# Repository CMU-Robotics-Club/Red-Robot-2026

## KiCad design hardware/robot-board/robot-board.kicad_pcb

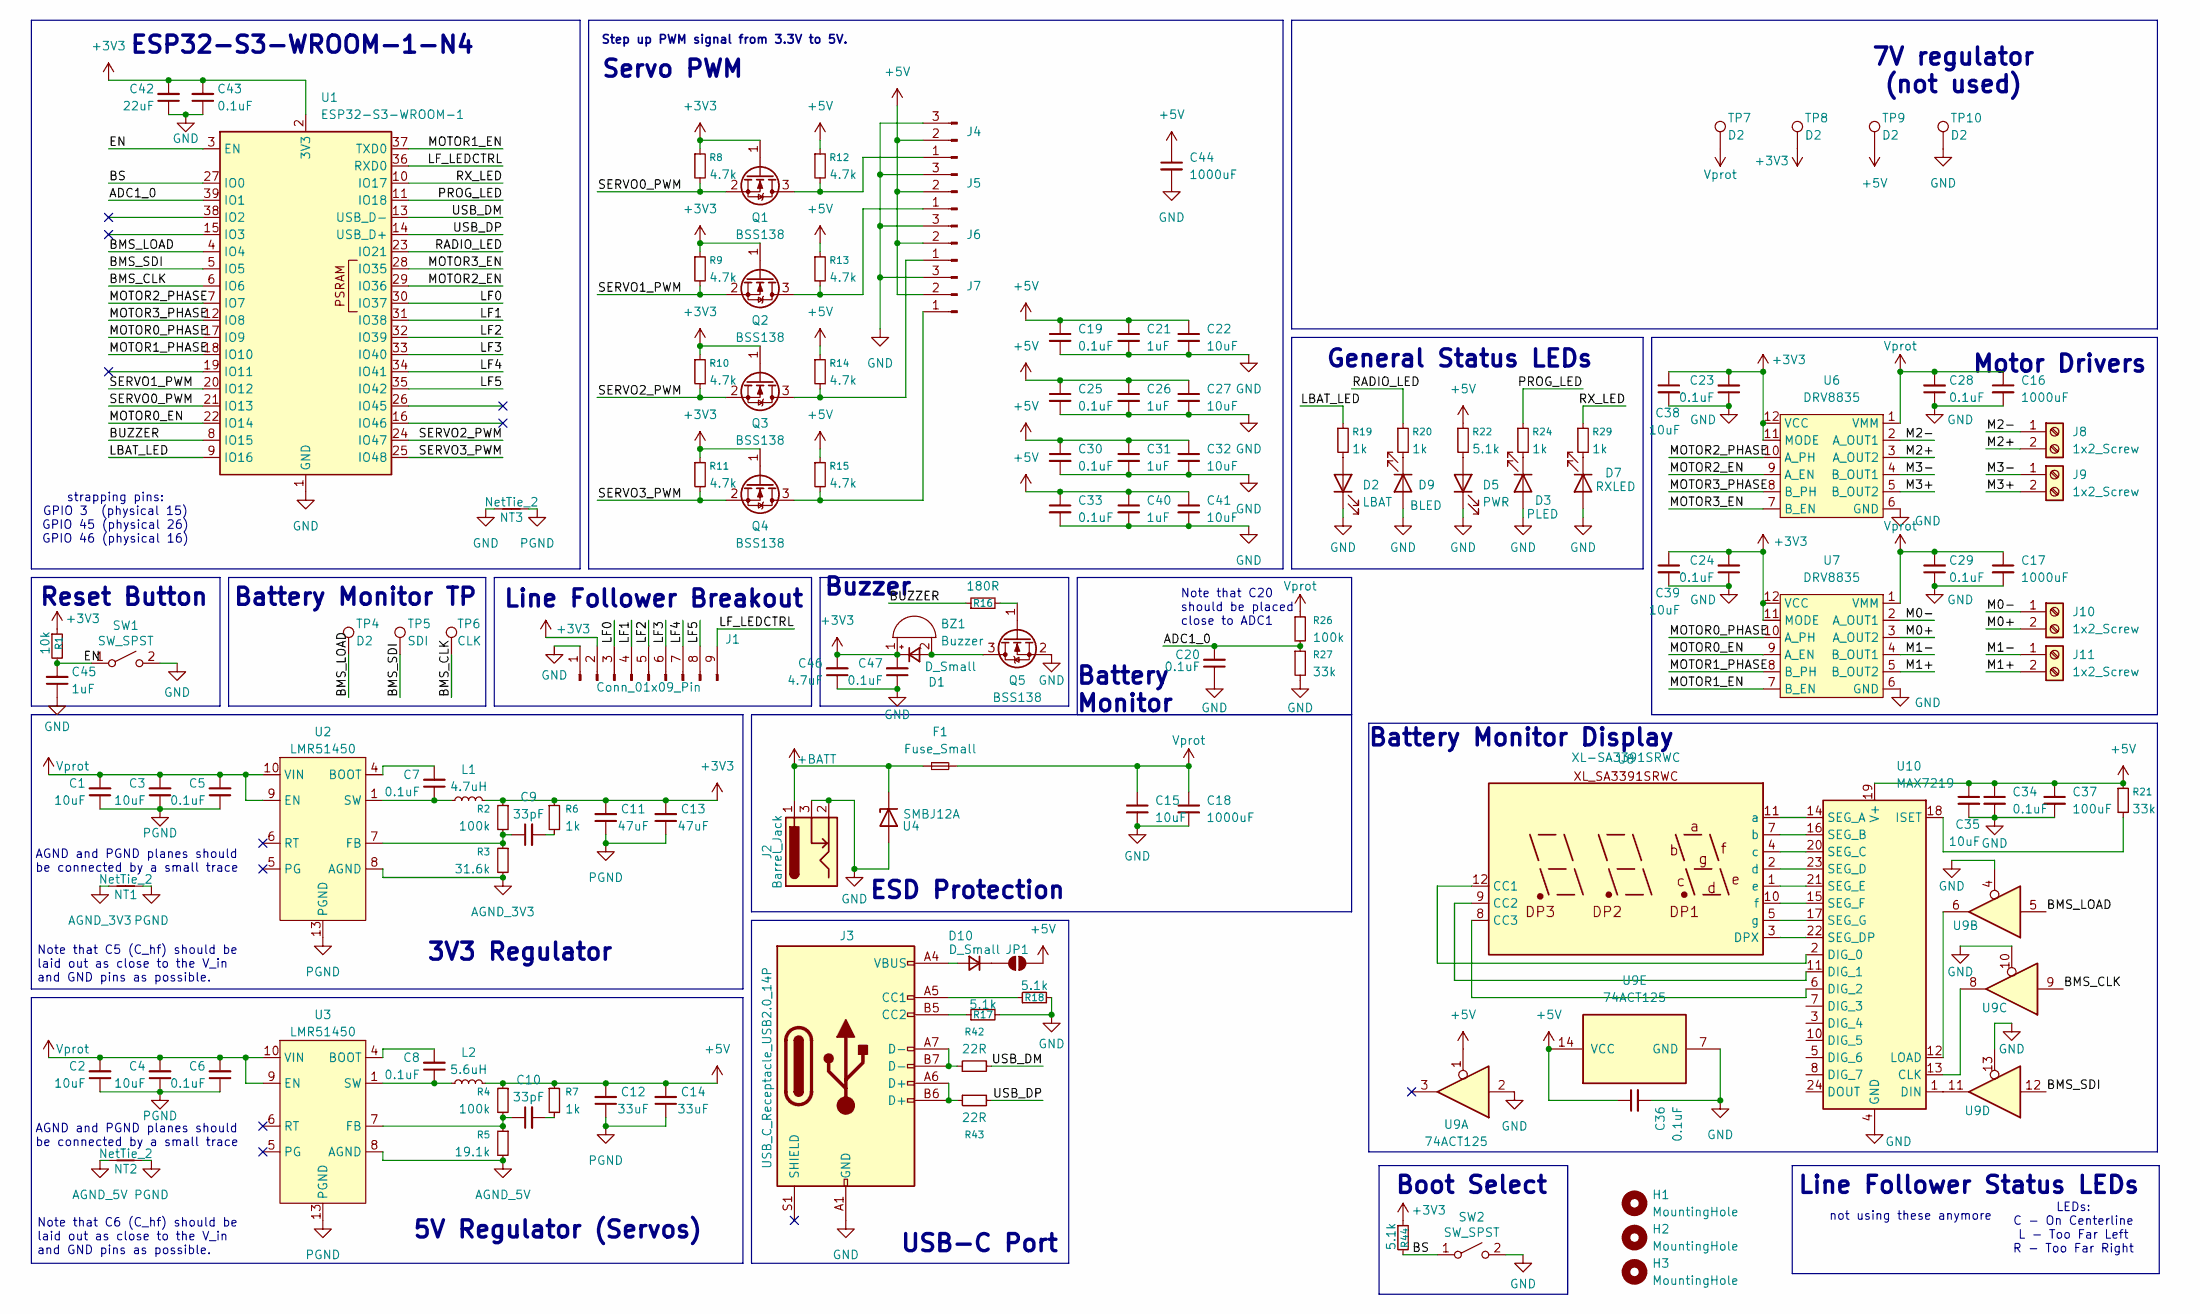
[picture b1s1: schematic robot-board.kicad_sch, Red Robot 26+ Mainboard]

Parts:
BZ1: Buzzer; MLT-7525; JLC P/N C95299
C1, C2, C3, C4: 10uF; C_1206_3216Metric; JLC P/N C33546013
C5, C6, C7, C8, C19, C20, C23, C24, C25, C28, C29, C30, C33, C34, C36, C43, C47: 0.1uF; C_0402_1005Metric; JLC P/N C1525
C9, C10: 33pF; C_0402_1005Metric; JLC P/N C107005
C11, C13: 47uF; C_1206_3216Metric; JLC P/N C385907
C12, C14: 33uF; C_1206_3216Metric; JLC P/N C342307
C15, C22, C27, C32, C35, C38, C39, C41: 10uF; C_0805_2012Metric; JLC P/N C15850
C16, C17, C18: 1000uF; CP_Elec_10x10; JLC P/N C970714
C21, C26, C31, C40: 1uF; C_0805_2012Metric; JLC P/N C282734
C37: 100uF; C_0805_2012Metric; JLC P/N C141660
C42: 22uF; C_0805_2012Metric; JLC P/N C296720
C44: 1000uF; CP_Elec_8x10; JLC P/N C2910470
C45: 1uF; C_0402_1005Metric; JLC P/N C49210445
C46: 4.7uF; C_0805_2012Metric; JLC P/N C880382
D1, D10: D_Small; D_SOD-123; JLC P/N C82544
D2: LBAT; LED_1206_3216Metric; JLC P/N C125086
D3: PLED; LED_1206_3216Metric; JLC P/N C51933322
D5: PWR; LED_1206_3216Metric; JLC P/N C5123493
D7: RXLED; LED_1206_3216Metric; JLC P/N C51933322
D9: BLED; LED_1206_3216Metric; JLC P/N C375460
F1: Fuse_Small; Fuseholder_Littelfuse_Nano2_154x; JLC P/N C206916
H1, H2, H3: MountingHole; MountingHole_3.2mm_M3
J1: Conn_01x09_Pin; PinHeader_1x09_P2.54mm_Vertical_SMD_Pin1Left; JLC P/N C49423356
J2: Barrel_Jack; BarrelJack_CLIFF_FC681465S_SMT_Horizontal; JLC P/N C114916
J3: USB_C_Receptacle_USB2.0_14P; USB_C_Receptacle_GCT_USB4105-xx-A_16P_TopMnt_Horizontal; JLC P/N C2988369
J4, J5, J6, J7: Conn_01x03_Pin; PinHeader_1x03_P2.54mm_Vertical_SMD_Pin1Right; JLC P/N C5160786
J8, J9, J10, J11: 1x2_Screw; TerminalBlock_DB301V-3.5-2P-GN-H_1x02_P3.50mm_Horizontal; JLC P/N C695629
JP1: SolderJumper_2_Open; SolderJumper-2_P1.3mm_Open_Pad1.0x1.5mm
L1: 4.7uH; L_Bourns_SRP7028A_7.3x6.6mm; JLC P/N C51933838
L2: 5.6uH; L_Bourns_SRP7028A_7.3x6.6mm; JLC P/N C5351382
NT1, NT2: NetTie_2; NetTie-2_SMD_Pad0.25mm
NT3: NetTie_2; NetTie-2_SMD_Pad0.5mm
Q1, Q2, Q3, Q4, Q5: BSS138; SOT-23; JLC P/N C112239
R1: 10k; R_0402_1005Metric; JLC P/N C25744
R2, R4, R26: 100k; R_0603_1608Metric; JLC P/N C122538
R3: 31.6k; R_0603_1608Metric; JLC P/N C860829
R5: 19.1k; R_0603_1608Metric; JLC P/N C855669
R6, R7, R19, R20, R24, R29: 1k; R_0402_1005Metric; JLC P/N C11702
R8, R9, R10, R11, R12, R13, R14, R15: 4.7k; R_0402_1005Metric; JLC P/N C105871
R16: 180R; R_0402_1005Metric; JLC P/N C138045
R17, R18, R22, R44: 5.1k; R_0402_1005Metric; JLC P/N C25905
R21: 33k; R_0402_1005Metric; JLC P/N C25779
R27: 33k; R_0603_1608Metric; JLC P/N C705768
R42, R43: 22R; R_0402_1005Metric; JLC P/N C2929994
SW1, SW2: SW_SPST; SW_Push_SPST_TS-1088; JLC P/N C720477
TP4, TP7, TP8, TP9, TP10: D2; TestPoint_THTPad_2.0x2.0mm_Drill1.0mm
TP5: SDI; TestPoint_THTPad_2.0x2.0mm_Drill1.0mm
TP6: CLK; TestPoint_THTPad_2.0x2.0mm_Drill1.0mm
U1: ESP32-S3-WROOM-1; JLC P/N C2913197
U2, U3: LMR51450; WSON-12-1EP_3x3mm_P0.5mm_EP1.5x2.5mm; JLC P/N C5782413
U4: SMBJ12A; D_SMB; JLC P/N C151251
U6, U7: DRV8835; WSON-12-1EP_3x2mm_P0.5mm_EP1x2.65; JLC P/N C129328
U8: XL-SA3391SRWC; JLC P/N C49652877
U9: 74ACT125; TSSOP-14_4.4x5mm_P0.65mm; JLC P/N C52940839
U10: MAX7219; SOIC-24W_7.5x15.4mm_P1.27mm; JLC P/N C52476

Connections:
+3V3: BZ1.1 (+), C11.2, C13.2, C23.2, C24.2, C38.1, C39.1, C42.2, C43.2, C46.2, C47.2, D1.1 (K), J1.2, L1.2, Q1.1 (G), Q2.1 (G), Q3.1 (G), Q4.1 (G), R1.1, R2.1, R6.1, R8.1, R9.1, R10.1, R11.1, R44.1, TP8.1 (1_1), U1.2 (3V3), U6.11 (MODE), U6.12 (VCC), U7.11 (MODE), U7.12 (VCC)
+5V: C12.2, C14.2, C19.1, C21.1, C22.1, C25.1, C26.1, C27.1, C30.1, C31.1, C32.1, C33.1, C34.1, C35.1, C36.1, C37.1, C40.1, C41.1, C44.1, J4.2, J5.2, J6.2, J7.2, JP1.2 (B), L2.2, R4.1, R7.1, R12.1, R13.1, R14.1, R15.1, R21.1, R22.1, TP9.1 (1_1), U9.1, U9.14 (VCC), U10.19 (V+)
+BATT: F1.1, J2.1, U4.1 (K)
/ADC1_0: C20.2, R26.2, R27.1, U1.39 (IO1)
/BMS_CLK: TP6.1 (1_1), U1.6 (IO6), U9.9
/BMS_LOAD: TP4.1 (1_1), U1.4 (IO4), U9.5
/BMS_SDI: TP5.1 (1_1), U1.5 (IO5), U9.12
/BS: R44.2, SW2.1 (A), U1.27 (IO0)
/BUZZER: R16.1, U1.8 (IO15)
/EN: C45.2, R1.2, SW1.1 (A), U1.3 (EN)
/LBAT_LED: R19.1, U1.9 (IO16)
/LF0: J1.3, U1.30 (IO37)
/LF1: J1.4, U1.31 (IO38)
/LF2: J1.5, U1.32 (IO39)
/LF3: J1.6, U1.33 (IO40)
/LF4: J1.7, U1.34 (IO41)
/LF5: J1.8, U1.35 (IO42)
/LF_LEDCTRL: J1.9, U1.36 (RXD0)
/M0+: J10.2, U7.3 (A_OUT2)
/M0-: J10.1, U7.2 (A_OUT1)
/M1+: J11.2, U7.5 (B_OUT2)
/M1-: J11.1, U7.4 (B_OUT1)
/M2+: J8.2, U6.3 (A_OUT2)
/M2-: J8.1, U6.2 (A_OUT1)
/M3+: J9.2, U6.5 (B_OUT2)
/M3-: J9.1, U6.4 (B_OUT1)
/MOTOR0_EN: U1.22 (IO14), U7.9 (A_EN)
/MOTOR0_PHASE: U1.17 (IO9), U7.10 (A_PH)
/MOTOR1_EN: U1.37 (TXD0), U7.7 (B_EN)
/MOTOR1_PHASE: U1.18 (IO10), U7.8 (B_PH)
/MOTOR2_EN: U1.29 (IO36), U6.9 (A_EN)
/MOTOR2_PHASE: U1.7 (IO7), U6.10 (A_PH)
/MOTOR3_EN: U1.28 (IO35), U6.7 (B_EN)
/MOTOR3_PHASE: U1.12 (IO8), U6.8 (B_PH)
/PROG_LED: R24.1, U1.11 (IO18)
/RADIO_LED: R20.1, U1.23 (IO21)
/RX_LED: R29.1, U1.10 (IO17)
/SERVO0_PWM: Q1.2 (S), R8.2, U1.21 (IO13)
/SERVO1_PWM: Q2.2 (S), R9.2, U1.20 (IO12)
/SERVO2_PWM: Q3.2 (S), R10.2, U1.24 (IO47)
/SERVO3_PWM: Q4.2 (S), R11.2, U1.25 (IO48)
/USB_DM: R42.2, U1.13 (USB_D-)
/USB_DP: R43.2, U1.14 (USB_D+)
AGND_3V3: NT1.1, R3.2, U2.8 (AGND)
AGND_5V: NT2.1, R5.2, U3.8 (AGND)
GND: C15.2, C16.2, C17.2, C18.2, C19.2, C20.1, C21.2, C22.2, C23.1, C24.1, C25.2, C26.2, C27.2, C28.1, C29.1, C30.2, C31.2, C32.2, C33.2, C34.2, C35.2, C36.2, C37.2, C38.2, C39.2, C40.2, C41.2, C42.1, C43.1, C44.2, C45.1, C46.1, C47.1, D2.1 (K), D3.2 (A), D5.1 (K), D7.2 (A), D9.2 (A), J1.1, J2.2, J2.3, J3.A1 (GND), J3.A12 (GND), J3.B1 (GND), J3.B12 (GND), J4.3, J5.3, J6.3, J7.3, NT3.1, Q5.2 (S), R17.2, R18.2, R27.2, SW1.2 (B), SW2.2 (B), TP10.1 (1_1), U1.1 (GND), U1.40 (GND), U1.41 (GND), U4.2 (A), U6.6 (GND), U6.13 (GND), U7.6 (GND), U7.13 (GND), U9.2, U9.4, U9.7 (GND), U9.10, U9.13, U10.4 (GND), U10.9 (GND)
unnamed: BZ1.2 (-), D1.2 (A), Q5.3 (D)
unnamed: C7.1, L1.1, U2.1 (SW), U2.2 (SW), U2.3 (SW)
unnamed: C8.1, L2.1, U3.1 (SW), U3.2 (SW), U3.3 (SW)
unnamed: C9.2, R6.2
unnamed: C10.2, R7.2
unnamed: D2.2 (A), R19.2
unnamed: D3.1 (K), R24.2
unnamed: D5.2 (A), R22.2
unnamed: D7.1 (K), R29.2
unnamed: D9.1 (K), R20.2
unnamed: D10.2 (A), J3.A4 (VBUS), J3.A9 (VBUS), J3.B4 (VBUS), J3.B9 (VBUS)
unnamed: D10.1 (K), JP1.1 (A)
unnamed: J3.A5 (CC1), R18.1
unnamed: J3.B5 (CC2), R17.1
unnamed: J3.A6 (D+), J3.B6 (D+), R43.1
unnamed: J3.A7 (D-), J3.B7 (D-), R42.1
unnamed: J4.1, Q1.3 (D), R12.2
unnamed: J5.1, Q2.3 (D), R13.2
unnamed: J6.1, Q3.3 (D), R14.2
unnamed: J7.1, Q4.3 (D), R15.2
unnamed: Q5.1 (G), R16.2
unnamed: C7.2, U2.4 (BOOT)
unnamed: C9.1, R2.2, R3.1, U2.7 (FB)
unnamed: C8.2, U3.4 (BOOT)
unnamed: C10.1, R4.2, R5.1, U3.7 (FB)
unnamed: U9.8, U10.13 (CLK)
unnamed: U8.12 (CC1), U10.2 (DIG_0)
unnamed: U8.9 (CC2), U10.11 (DIG_1)
unnamed: U8.8 (CC3), U10.6 (DIG_2)
unnamed: U9.11, U10.1 (DIN)
unnamed: R21.2, U10.18 (ISET)
unnamed: U9.6, U10.12 (LOAD)
unnamed: U8.11 (a), U10.14 (SEG_A)
unnamed: U8.7 (b), U10.16 (SEG_B)
unnamed: U8.4 (c), U10.20 (SEG_C)
unnamed: U8.2 (d), U10.23 (SEG_D)
unnamed: U8.3 (DPX), U10.22 (SEG_DP)
unnamed: U8.1 (e), U10.21 (SEG_E)
unnamed: U8.10 (f), U10.15 (SEG_F)
unnamed: U8.5 (g), U10.17 (SEG_G)
PGND: C1.1, C2.1, C3.1, C4.1, C5.1, C6.1, C11.1, C12.1, C13.1, C14.1, NT1.2, NT2.2, NT3.2, U2.13 (PGND), U3.13 (PGND)
Vprot: C1.2, C2.2, C3.2, C4.2, C5.2, C6.2, C15.1, C16.1, C17.1, C18.1, C28.2, C29.2, F1.2, R26.1, TP7.1 (1_1), U2.9 (EN), U2.10 (VIN), U2.11 (VIN), U2.12 (VIN), U3.9 (EN), U3.10 (VIN), U3.11 (VIN), U3.12 (VIN), U6.1 (VMM), U7.1 (VMM)

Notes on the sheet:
Line Follower Status LEDs
Battery Monitor
ESD Protection
Boot Select
Motor Drivers
Note that C20 should be placed close to ADC1
Reset Button
3V3 Regulator
Battery Monitor Display
Servo PWM
Note that C5 (C_hf) should be laid out as close to the V_in and GND pins as possible.
AGND and PGND planes should be connected by a small trace
not using these anymore
ESP32-S3-WROOM-1-N4
Note that C6 (C_hf) should be laid out as close to the V_in and GND pins as possible.
strapping pins: GPIO 3 (physical 15) GPIO 45 (physical 26) GPIO 46 (physical 16)
Battery Monitor TP
5V Regulator (Servos)
Line Follower Breakout
Step up PWM signal from 3.3V to 5V.
Buzzer
USB-C Port
General Status LEDs
LEDs: C - On Centerline L - Too Far Left R - Too Far Right
7V regulator (not used)

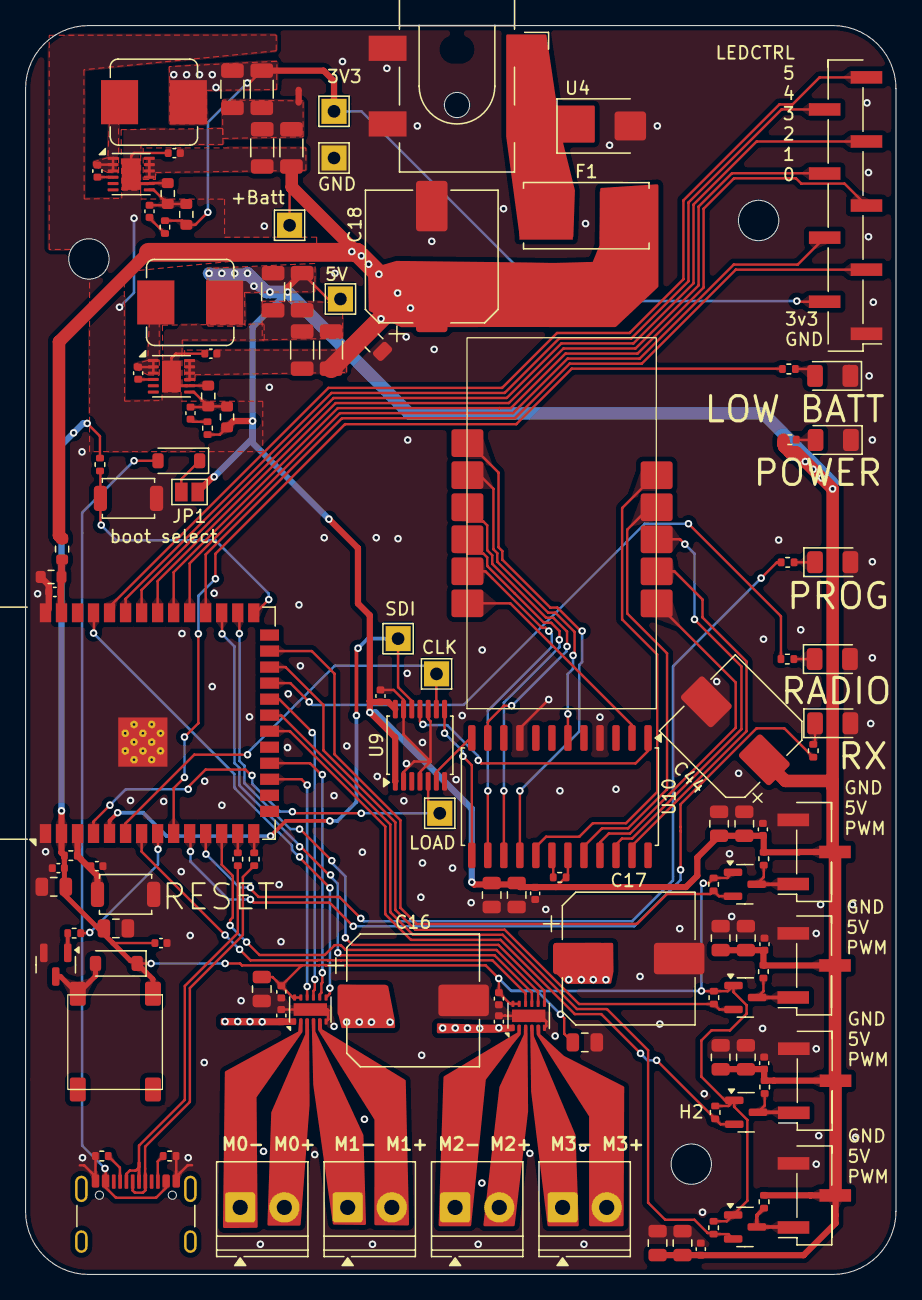
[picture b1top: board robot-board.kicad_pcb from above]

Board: 4 copper layers, 69.0 x 99.0 mm, 128 parts (0 on the bottom side), 88 nets.

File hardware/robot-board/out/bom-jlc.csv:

Comment,Designator,Footprint,LCSC Part Number
"BLED: Light emitting diode, blue",D9,LED_SMD:LED_1206_3216Metric,C375460
"RXLED: Light emitting diode, orange",D7,LED_SMD:LED_1206_3216Metric,C51933322
"PWR: Light emitting diode, green",D5,LED_SMD:LED_1206_3216Metric,C5123493
"PLED: Light emitting diode, orange",D3,LED_SMD:LED_1206_3216Metric,C51933322
"LBAT: Light emitting diode, red",D2,LED_SMD:LED_1206_3216Metric,C125086
"D_Small: Diode, small symbol","D1,D10",Diode_SMD:D_SOD-123,C82544
MAX7219: 8-Digit LED Display Driver,U10,Package_SO:SOIC-24W_7.5x15.4mm_P1.27mm,C52476
74ACT125: Quadruple Bus Buffer Gates With 3-State Outputs,U9,Package_SO:TSSOP-14_4.4x5mm_P0.65mm,C52940839
XL-SA3391SRWC: 3 Digit 7-Segment Display,U8,Display_7Segment:XL-SA3391SRWC,C49652877
DRV8835: ,"U6,U7",Package_SON:WSON-12-1EP_3x2mm_P0.5mm_EP1x2.65,C129328
SMBJ12A: TVS diode,U4,Diode_SMD:D_SMB,C151251
LMR51450: ,"U2,U3",Package_SON:WSON-12-1EP_3x3mm_P0.5mm_EP1.5x2.5mm,C5782413
"ESP32-S3-WROOM-1: RF Module, ESP32-S3 SoC, Wi-Fi 802.11b/g/n, Bluetooth, BLE, 32-bit, 3.3V, onboard antenna, SMD",U1,RF_Module:ESP32-S3-WROOM-1,C2913197
SW_SPST: Single Pole Single Throw (SPST) switch,"SW1,SW2",footprints:SW_Push_SPST_TS-1088,C720477
"22R: Resistor, small symbol","R42,R43",Resistor_SMD:R_0402_1005Metric,C2929994
"33k: Resistor, small symbol",R27,Resistor_SMD:R_0603_1608Metric,C705768
"33k: Resistor, small symbol",R21,Resistor_SMD:R_0402_1005Metric,C25779
"5.1k: Resistor, small symbol","R17,R18,R22,R44",Resistor_SMD:R_0402_1005Metric,C25905
"180R: Resistor, small symbol",R16,Resistor_SMD:R_0402_1005Metric,C138045
"4.7k: Resistor, small symbol","R8,R9,R10,R11,R12,R13,R14,R15",Resistor_SMD:R_0402_1005Metric,C105871
"1k: Resistor, small symbol","R6,R7,R19,R20,R24,R29",Resistor_SMD:R_0402_1005Metric,C11702
"19.1k: Resistor, small symbol",R5,Resistor_SMD:R_0603_1608Metric,C855669
"31.6k: Resistor, small symbol",R3,Resistor_SMD:R_0603_1608Metric,C860829
"100k: Resistor, small symbol","R2,R4,R26",Resistor_SMD:R_0603_1608Metric,C122538
"10k: Resistor, small symbol",R1,Resistor_SMD:R_0402_1005Metric,C25744
"BSS138: 50V Vds, 0.22A Id, N-Channel MOSFET, SOT-23","Q1,Q2,Q3,Q4,Q5",Package_TO_SOT_SMD:SOT-23,C112239
"5.6uH: Inductor, small symbol",L2,Inductor_SMD:L_Bourns_SRP7028A_7.3x6.6mm,C5351382
"4.7uH: Inductor, small symbol",L1,Inductor_SMD:L_Bourns_SRP7028A_7.3x6.6mm,C51933838
1x2_Screw: ,"J8,J9,J10,J11",footprints:TerminalBlock_DB301V-3.5-2P-GN-H_1x02_P3.50mm_Horizontal,C695629
"Conn_01x03_Pin: Generic connector, single row, 01x03, script generated","J4,J5,J6,J7",Connector_PinHeader_2.54mm:PinHeader_1x03_P2.54mm_Vertical_SMD_Pin1Right,C5160786
USB_C_Receptacle_USB2.0_14P: USB 2.0-only 14P Type-C Receptacle connector,J3,footprints:USB_C_Receptacle_GCT_USB4105-xx-A_16P_TopMnt_Horizontal,C2988369
Barrel_Jack: DC Barrel Jack with an internal switch,J2,Connector_BarrelJack:BarrelJack_CLIFF_FC681465S_SMT_Horizontal,C114916
"Conn_01x09_Pin: Generic connector, single row, 01x09, script generated",J1,Connector_PinHeader_2.54mm:PinHeader_1x09_P2.54mm_Vertical_SMD_Pin1Left,C49423356
"Fuse_Small: Fuse, small symbol",F1,Fuse:Fuseholder_Littelfuse_Nano2_154x,C206916
"4.7uF: Unpolarized capacitor, small symbol",C46,Capacitor_SMD:C_0805_2012Metric,C880382
"1uF: Unpolarized capacitor, small symbol",C45,Capacitor_SMD:C_0402_1005Metric,C49210445
"1000uF: Unpolarized capacitor, small symbol",C44,Capacitor_SMD:CP_Elec_8x10,C2910470
"22uF: Unpolarized capacitor, small symbol",C42,Capacitor_SMD:C_0805_2012Metric,C296720
"100uF: Unpolarized capacitor, small symbol",C37,Capacitor_SMD:C_0805_2012Metric,C141660
"1uF: Unpolarized capacitor, small symbol","C21,C26,C31,C40",Capacitor_SMD:C_0805_2012Metric,C282734
"1000uF: Unpolarized capacitor, small symbol","C16,C17,C18",Capacitor_SMD:CP_Elec_10x10,C970714
"10uF: Unpolarized capacitor, small symbol","C15,C22,C27,C32,C35,C38,C39,C41",Capacitor_SMD:C_0805_2012Metric,C15850
"33uF: Unpolarized capacitor, small symbol","C12,C14",Capacitor_SMD:C_1206_3216Metric,C342307
"47uF: Unpolarized capacitor, small symbol","C11,C13",Capacitor_SMD:C_1206_3216Metric,C385907
"33pF: Unpolarized capacitor, small symbol","C9,C10",Capacitor_SMD:C_0402_1005Metric,C107005
"0.1uF: Unpolarized capacitor, small symbol","C5,C6,C7,C8,C19,C20,C23,C24,C25,C28,C29,C30,C33,C34,C36,C43,C47",Capacitor_SMD:C_0402_1005Metric,C1525
"10uF: Unpolarized capacitor, small symbol","C1,C2,C3,C4",Capacitor_SMD:C_1206_3216Metric,C33546013
"Buzzer: Buzzer, polarized",BZ1,Buzzer_Beeper:MLT-7525,C95299

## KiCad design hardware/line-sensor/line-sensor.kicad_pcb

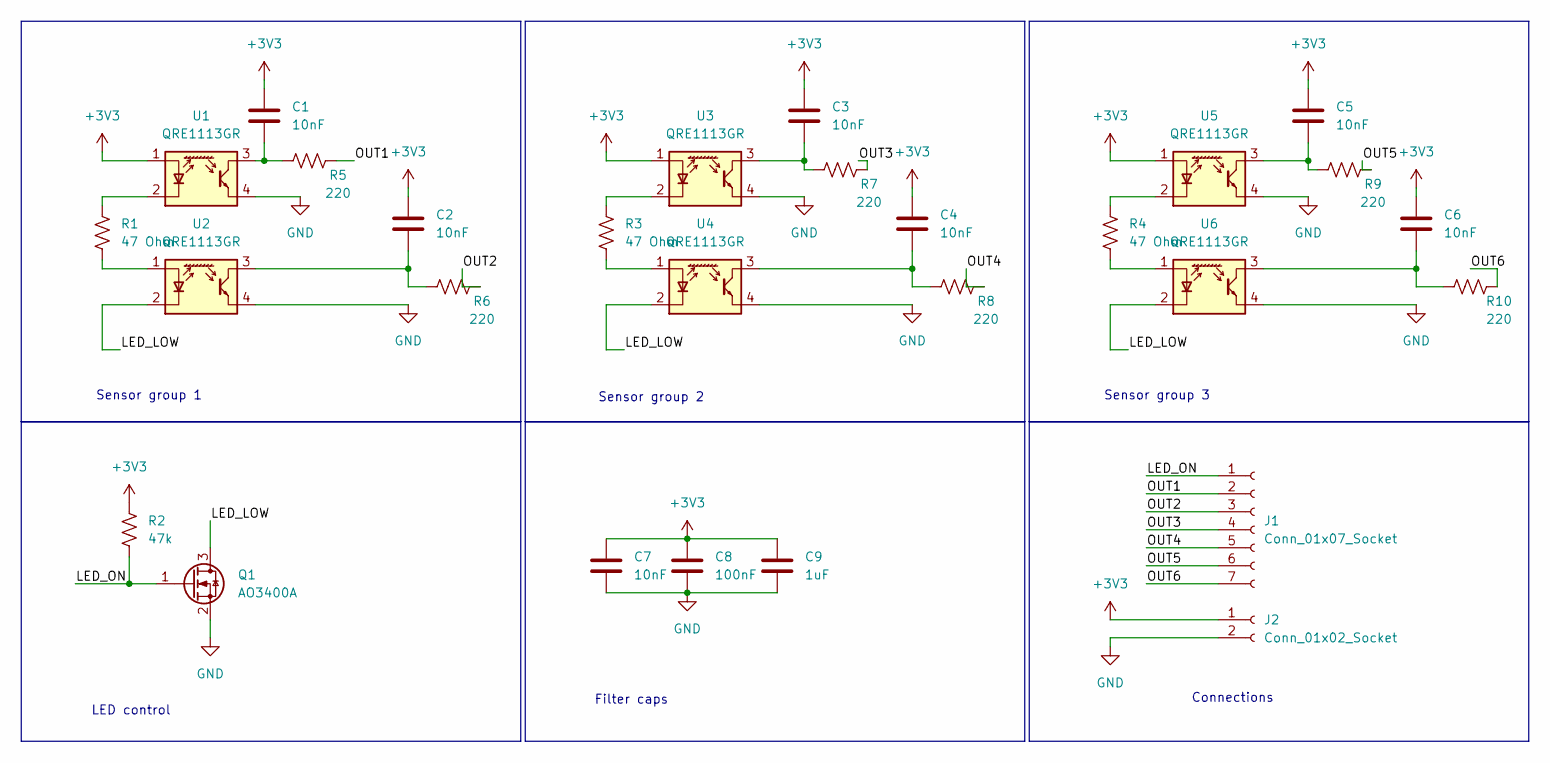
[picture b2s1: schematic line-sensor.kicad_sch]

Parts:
C1, C2, C3, C4, C5, C6, C7: 10nF; C_0603_1608Metric_Pad1.08x0.95mm_HandSolder
C8: 100nF; C_0603_1608Metric_Pad1.08x0.95mm_HandSolder
C9: 1uF; C_0603_1608Metric_Pad1.08x0.95mm_HandSolder
J1: Conn_01x07_Socket; PinHeader_1x07_P2.54mm_Vertical_SMD_Pin1Left; LCSC C42379199
J2: Conn_01x02_Socket; PinSocket_1x02_P2.54mm_Vertical_SMD_Pin1Right; LCSC C42381025
Q1: AO3400A; SOT-23; LCSC C20917
R1, R3, R4: 47 Ohm; R_0603_1608Metric_Pad0.98x0.95mm_HandSolder
R2: 47k; R_0603_1608Metric_Pad0.98x0.95mm_HandSolder
R5, R6, R7, R8, R9, R10: 220; R_0603_1608Metric_Pad0.98x0.95mm_HandSolder
U1, U2, U3, U4, U5, U6: QRE1113GR; OnSemi_CASE100CY; LCSC C232862

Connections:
+3V3: C1.1, C2.1, C3.1, C4.1, C5.1, C6.1, C7.1, C8.1, C9.1, J2.1, R2.1, U1.1 (A), U3.1 (A), U5.1 (A)
/LED_LOW: Q1.3 (D), U2.2 (K), U4.2 (K), U6.2 (K)
/LED_ON: J1.1, Q1.1 (G), R2.2
/OUT1: J1.2, R5.2
/OUT2: J1.3, R6.2
/OUT3: J1.4, R7.2
/OUT4: J1.5, R8.2
/OUT5: J1.6, R9.2
/OUT6: J1.7, R10.2
GND: C7.2, C8.2, C9.2, J2.2, Q1.2 (S), U1.4, U2.4, U3.4, U4.4, U5.4, U6.4
unnamed: C1.2, R5.1, U1.3
unnamed: C2.2, R6.1, U2.3
unnamed: C3.2, R7.1, U3.3
unnamed: C4.2, R8.1, U4.3
unnamed: C5.2, R9.1, U5.3
unnamed: C6.2, R10.1, U6.3
unnamed: R1.1, U1.2 (K)
unnamed: R1.2, U2.1 (A)
unnamed: R3.1, U3.2 (K)
unnamed: R3.2, U4.1 (A)
unnamed: R4.1, U5.2 (K)
unnamed: R4.2, U6.1 (A)

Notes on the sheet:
Sensor group 2
Sensor group 3
Filter caps
LED control
Sensor group 1
Connections

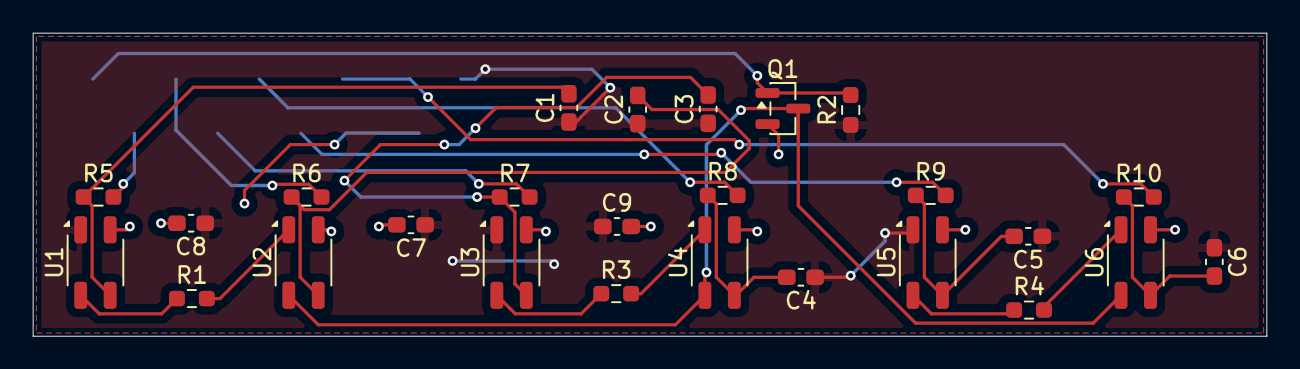
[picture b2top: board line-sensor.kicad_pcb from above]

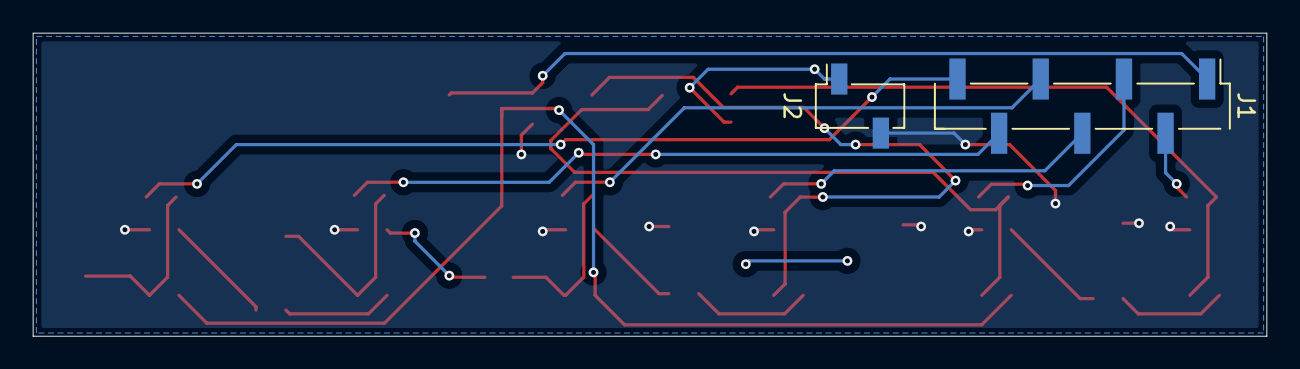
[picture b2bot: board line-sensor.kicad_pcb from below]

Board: 2 copper layers, 75.3 x 18.5 mm, 28 parts (2 on the bottom side), 22 nets.

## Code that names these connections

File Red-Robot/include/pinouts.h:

/**
 * @file  pinouts.h
 * @brief ESP32 pinout map
 *
 * Nets should match name with schematic
 */

#pragma once

// Motors
#define MOTOR0_PHASE 9
#define MOTOR1_PHASE 10
#define MOTOR2_PHASE 7
#define MOTOR3_PHASE 8

#define MOTOR0_EN 14
#define MOTOR1_EN 43 // TXD0
#define MOTOR2_EN 36
#define MOTOR3_EN 35

// Servo PWM
#define SERVO0_PWM 13
#define SERVO1_PWM 12
#define SERVO2_PWM 47
#define SERVO3_PWM 48

// Buzzer
#define BUZZER 15

// Status LEDs
#define LBAT_LED 16
#define RADIO_LED 21
#define RX_LED 17
#define PROG_LED 18

// Line following
#define LF0 37
#define LF1 38
#define LF2 39
#define LF3 40
#define LF4 41
#define LF5 42
#define LF_LEDCTRL 43 // RXD0

// BMS
#define BMS_LOAD 4
#define BMS_SDI 5
#define BMS_CLK 6

// Battery voltage divider
#define ADC1_0 1

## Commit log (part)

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2026-01-18 created robot pcb project file
    and added symbol and footprint for esp
2026-01-22 repo cleanup: added gitignore
    * deleted symbol files for esp module (they're auto-included with kicad
    libraries)
    * deleted backup files from last commit
2026-01-22 added "outline" for robot pcb
2026-01-30 many changes
    power management, status lights, servo control, BMS (waiting for mithun), ESD protection
2026-01-31 added folder for code, set up pio
    * pio configured for ESP32-S3-Devkit
    * WIP code for controlling 7 segment display via shift register
    * tested, currently not functional. maybe the extra time delays will
    help
2026-02-04 initial line sensor schematic
2026-02-04 added power conn
2026-02-04 added LCSC part number to schematic
2026-02-06 finished most of schematic
2026-02-06 fixed a bunch of bs
2026-02-06 schematic basically done
2026-02-06 BOM and changed footprints
2026-02-06 Added schematic for 7 segment display
2026-02-06 Placed 7segdisplay in the correct folder, fuck you Matthew
2026-02-06 bnyahaj
    bnyahaj
2026-02-17 Inserted the new 7 segment display wiring to be later added to the full pcb design
2026-02-17 Fixed 7segmentdisplay sch file to include version 1 and 2a and 2b
2026-02-18 changed some stuff idk highkey
2026-02-20 fixed 7seg
2026-02-23 JLCPCB BOM and P&P files (default ones didnt work)
2026-02-23 Not sure why this wasn't committed
2026-03-12 added buzzer, battery LCD, etc
2026-03-19 layout!
2026-03-20 fixed some stuff
2026-03-20 who up roboing their club
2026-03-20 uhhh i hope this works, delaynie
2026-03-23 gerbers n stuff hi hi
2026-04-13 fixed the thingies
2026-04-23 fixed footprint/part mismatch
2026-06-29 fixed all issues, removed LF LEDs
